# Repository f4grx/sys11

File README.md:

sys11
=====

This is a development board for the 68hc11 microcontroller.

The goal is to build a robust, simple, reliable, and repairable computer from
scrap, similar to what collapseOS is seeking.

The project defines two ROM images:
* a shell interface with assemble-time modular commands, development is halted.
* a forth interpreter.

Forth is a portable stack supported language wich is surprisingly powerful, even on
small targets. It has the potential to describe complex programs in a very compact way.

A lot of resources about forth are available online. This project defines a minimally small
forth interpreter with indirect threading. The goal is to build a 68hc11 interpreter that can
be used to write the interpreter itself, so it has to be as small as possible.

CPU: 68HC11A0, the most basic one. This is what I found in my drawer, and is
more desirable than a basic 6502 or other because it has integrated peripherals.
I only choose chips that I have replacement for.

Clock speed: 8 MHz XTAL / OSC, which translates to 2 MHz internal and
bus clock (Cycle time 500 ns). It seems that 16 MHz (4 MHz E clock, 250 ns
cycle) is also working. May switch to that later.

Currently sys11 is implemented on a protoboard using soldered 30AWG (wirewrap)
wires.

Memory map (HC11 extended mode)
-------------------------------

* Internal RAM kept mapped at 0x0000
* Memory Mapped Registers mapped at 0x0000 (unusual). They overlay the internal
RAM, which means internal RAM locations 00h..3Fh are not usable (except the
locations that are reserved or related to PORTB and PORTC: 0002h-0007h).

* 32KB On-board Main SRAM (62256) in 0000h - 7FFFh CSRAM = A15
* 16KB Off-board secondary SRAM (half 62256) in 8000h - BFFFh, possibly banked
for additional space using a IO register. Then we could use an even bigger RAM
chip. CSXRAM = !(A15 & !A14)
* 8KB I/O space with 8 CS lines in C000h - DFFFh (1KB per CS)
CSIO = !(A15 & A14 & !A13)
* 8KB EPROM in E000h - FFFFh - monitor and SPI flash loader. For development,
this chip can be replaced with a RAM/EEPROM/NVRAM, the board actually use a
DIL32 socket instead of 28, that exposes the nWR line. An additional pair of DIL
sockets can be used to route this signal to the actual /WR line of the debug
RAM. This is actually using a 27256 EPROM with 4 manually selected banks, to
allow for different boot images (asm, communications, shell, storage mgmt, TBD)
CSROM = !(A15 & A14 & A13)
* External bus lines are only driven when external bus is actually addressed.
It is not driven when the on-board memory (32K RAM, 8K ROM) is addressed.
CSEXT = CSIO & CSXRAM

Main address decoding can be done with a few NAND gates (7400 2-input, and 7410
3-input NAND gates).

Peripherals
-----------

* 5V power from USB
* SCI : (UART), TX and RX lines on a pin header for external communication.
10K pullups are installed to ensure proper behaviour in bootstrap mode where
PORTD is configured as open drain.
* HE10-40 connector for external bus. All lines buffered by 74xx245.

Seriously planned features
--------------------------

* Robust 5V power supply (LF50 LDO, max voltage 40V) with reverse voltage
protection
* Additional LM2575 step-down to reduce LDO heating (bypassable).
* 3 outputs (PORTA) dedicated as SPI CS selector lines (3 bits + 74138 decoder +
normal /SS line)
* I2C bus using discrete N-MOS transistor on OC lines to drive the bus in open
* Multi-VPP EPROM programmer on a secondary board
* Fully shielded aluminum enclosure for a 100x160 board

Planned vaporware features
--------------------------

* Removable SPI/I2C flash cardriges
* SCSI
* Ethernet
* MCP2515 SPI CAN
* Additional UARTs and various comm interfaces (fiber, RS422 RS485...)
* Wireless communication interfaces (AX.25, 1200 bauds packet modem)
* Audio cassette program storage (Kansas)
* Dual-port RAM in IO space for communication and shared mem with another HC11.

What is already done
--------------------
* Memory map
* Schematic (includes errors)
* I have some chips: 4x 68HC11A0, 1x 68HC11A1, 1x 68HC11E2 (thanks vince),
some 74xx245, 573, 138, 00, 10, 27256, various 32Kx8 and 8Kx8 RAMs
* Ordered a 2864 EEPROM from ebay (received, meanwhile I found another one in a junkbox)
* Bootstrap uploader in Python3.
* Working hardware prototype on 100x160 perforated board
* Clock, Reset, UART connection, power supply with decoupling
* Memory map decoder using logic gates
* The HC11 starts in bootstrap mode and successfully executes code to drive LED.
* The HC11 is able to select the expanded mode and test the 32K RAM without
  errors (and also a RAM in the dedicated 8K EPROM space).
* bootstrap program to load more memory. Initally planned to use a custom HDLC
  protocol, but will rather load S-records directly.
* IRQ lines from expansion board to cpu (were broken due to lack of pullups)

Summary: The system is validated on the soldered wirewrap euro board.

What remains to be done
-----------------------
* Editing schematic to fix errors and match reality of prototype
* Finish simulating all opcodes
* Replace fifth LS245 registers with sth that allows open drain on RST and IRQs.
* Determine next step for hardware. Secondary board with more RAM? EPROM programmer?
* NVRAM SSD using these old bq4017 samples maxim generously offered me for free
  multiple years ago (Unfortunately this board will be a one-of-a-kind add-on
  unless you have these chips available or are able to find enough RAM chips)
* Some kind of documentation storage using big EEPROMs (27C040/27C080) mapped in IO
  space using a 256-byte window. This would allow use as block storage. Same idea
  applies to the bq4017 nvrams.
* I2C bus hardware
* Design a smaller PCB that can fit in a smaller shielded box.

Software roadmap
----------------
* Bootloader for extended mode - DONE
* Malloc - WIP, almost validated
* Simulator - WIP
* Basic shell - ABANDONED
* SPI bus driver - Should workd
* Block device system - ABANDONED
* Forth - WIP

* SPI and/or I2C EEPROM driver
* I2C bus driver

Abandoned features that should be implementable in forth
--------------------------------------------------------
* Assembler
* Self host the system

Abandoned features that are useless or too complex
--------------------------------------------------
Or may be done later...
* ed-based text editor
* Definition of a position independent binary format
* IO kernel
* Program loader
* RTOS

SPI bus
-------
The HC11 hardware SPI bus wil be used in master mode.
* The SS line is used as OE for a 74138 decoder that provides 8 CS lines from
3 OC lines of port A.

I2C bus
-------
A proper i2c bus needs two bidirectionnal open drain lines, which are not
available on the HC11 if one wants to benefit from the hardware SPI block on
PORTD. Moreover, the HC11 does not have a hardware i2c, so bitbanging must be
used.

The i2c bus will be done on port A using Input Capture and Output Compare lines.
To read SDA and SCL, the IC1 and IC2 lines are used. To write the bus, the OC1
and OC2 lines are used to drive small BS170 MOSFETs. This requires inversion of
the bits to write, which is not a big problem for the driver.

FAQ
---
Q: Why move to Forth?

A: At first I did not want it, and I planned to build an assembler and shell to
be able to compile source assembly files and rebuild the system from itself.
While doable, this will use a lot of memory, both flash and RAM. Just a shell and
still-not-working block device system was using 800 bytes, or 1/10 of the rom space.

It is pitiful to have 8k of ROM and only be able to have an assembler program, and
nothing else.

Meanwhile CollapseOS, which was going in the same direction, realized the potential
of forth and started implementing it. I followed the movement for several reasons:
* Forth is portable, the same routines are able to work on "any" forth implementing
machine, whatever the underlying CPU. This greatly increases the potential of collapse
recovery machines.
* It is still possible to write an assembler in forth, even cross assemblers are possible,
which still increases the ability to mix different machine in a portable software environment.
* It has the potential to express quite complex software constructs in a very compact manner

Q: Why not use a 6502?

A: Because the 6502 has a 8-bit stack pointer which is ridiculously restrictive.
We are not anymore in the situation where the 6800 was $179 and the 6502 was $29.

A2: Going to forth, the underlying CPU is not so important since Forth can be implemented
on a variety of machines.

Q: Why not use a Z80?

A: Because I did not have one when I started this project. However, I plan to
have an assembler for this target. If you want to play with the Z80, have a
look at the RC2014 project and/or github.com/hsoft/collapseos.

The HC11 is a microcontroller, which usefully comes with an integrated UART and
SPI peripherals. The Z80 does not, so it requires external bus peripherals.
However, the Z80 can hook these devices to its IO bus, saving space for more RAM
on the memory bus.

At some point it may be more interesting to build a Z80 system, to benefit from
more RAM, and also more registers, even if the Z80 requires more cycles to
execute every instruction.

Other CPUs are also interesting to increase the potential for collapse recovery:
ARM and MSP430 are such interesting targets, even the x86.

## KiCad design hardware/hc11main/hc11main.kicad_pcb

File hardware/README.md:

sys11 hardware
===================

The most important part of this subproject is the schematic, that defines all
the components and their connection.

The circuit board can either be as a real two-sided PCB with SMD components for
compacity (the full SMD system can fit in a ebay 100x76x35 aluminium box).

But it can also be built on a pair of 100x160 prototyping boards, using a
HE10-40 and a ribbon cable, or a 64-pin Euro rack mount system. In that case,
connections can be either soldered or wirewrapped (!).

Design philosophy
-----------------
The secret goal of this project is to survive a technical apocalypse, even if
such an event is highly improbable and we would probably have more important
priorities than computers at that time.
Nevertheless, such a computer is interesting for educational purposes, and also
because it is likely much more robust and repairable than a modern computer.

BTW, if you want a more powerful computer, use an embedded ARM SoC (like stm32)
or a Raspberry Pi. However, if it breaks, dont ask me to fix it :p

Another goal of such a project is to allow programming of other computers
without having access to a more complex machine, so we will aim at developing
assemblers and uploaders for PIC, Arduino, and programmers for various memories
like EPROMS, EEPROMs, FLASHes, etc. that can be used in other designs.

Mini circuit board
------------------

The PCB and gerbers in this directory describe a board 100x70mm, that will fit
an ebay aluminium box of dimensions 100x76x35mm, using SMD components in SOIC
format. The resulting project is compact and somewhat repairable but requires a
lot of care not to burn the fine PCB traces. To help with repairs, each SMD
trace has two vias in it, which should reduce the risk of having lifted pads
when desoldering a SMD component. When desoldering a broken SMD component, it is
often desirable to limit PCB damage by cutting the chip leads with pliers, then
removing each of the still soldered leads one by one.

Connection between the two boards is achieved by a ribbon cable using straight pins
through the pcb, putting the ribbon cable in a u-shape. Board-to-board
stackable connectors can also be used.

Euro circuit board
------------------

This option is much larger but is much more robust than the mini circuit board.
All components can be removed and replaced, and connections can be reworked with
a lot of ease (just taking care not to burn the insulation of nearby wires).

Interconnections can use either soldered wirewrap 30AWG wire, or just plain
wirewrapping if sockets, tools and wires are available.

Connection between the two board is achieved by a ribbon wire on the side of the
boards, similar to what is used to connect IDE hard drives, except the full 40
pins are used, so the key usually found on IDE ribbon connector has to be
removed. The PCB is cut so that the socket and the plug of the ribbon do not
protrude outside of the euro board. This allows the user to build a simple and
robust metallic case from aluminum strips and flats.

Here is the current state of the prototype, top and bottom:

Enclosure
---------

Since one of the goal of this project is to bootstrap electronic circuits after
a civilization collapse, it is important to make sure that it can itself survive
the kind of difficult environment that may cause this collapse, including a
severe EMP event.

The only way to do that is to shield everything. So a proper metallic enclosure
has to be used. ebay has lot of extruded aluminium boxes suitable for both the
mini board and 100x160 boards. If the builder has machining resources, then it
is also possible to mill a box or build one from aluminium sheet and bars.

Connections are much more critical than the board itself. Since an EMP event
will induce high voltage in any wire that is not properly shielded, any
connector and opening in the project box is critical. I will only be using a
single SUB-D connector with the least amount of pins (probably 15). The
connector itself will receive a  metallic cover and will be disconnected when
the computer is not actively used.

Additional protections will be added on each electrical line crossing the box
through this SUBD connector: the possible components are gas discharge cells,
series resistors, and bidirectional transil diodes. The goal is to minimize the
impact of high voltages by reducing them to a low value if possible.

The ideal situation would be a single UART communication channel using
opto-isolated signals, like TOSLINK plastic optical fibers. Only the power supply would
then need severe EMP protections.

Prototype Progress
------------------

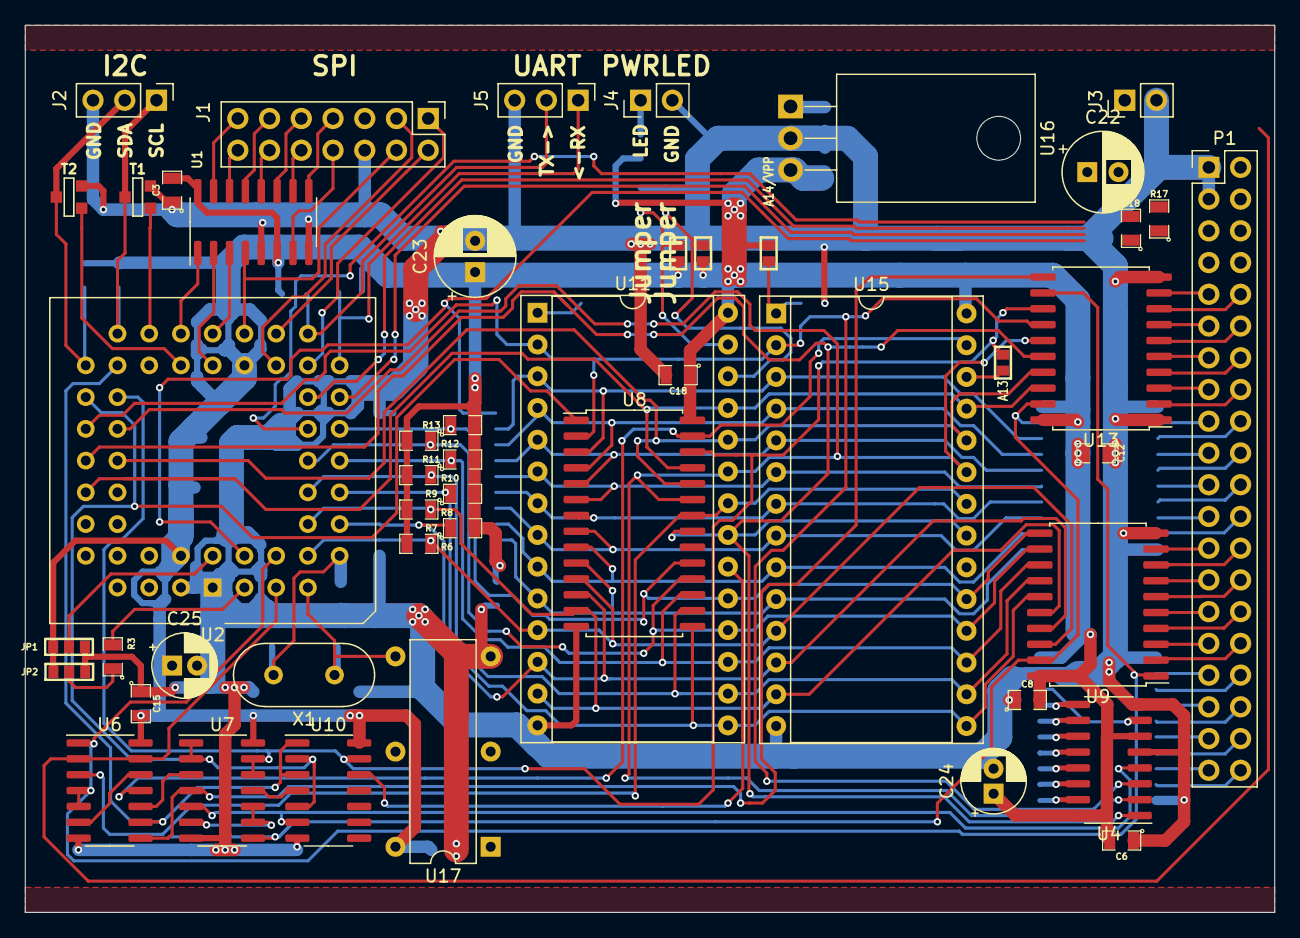
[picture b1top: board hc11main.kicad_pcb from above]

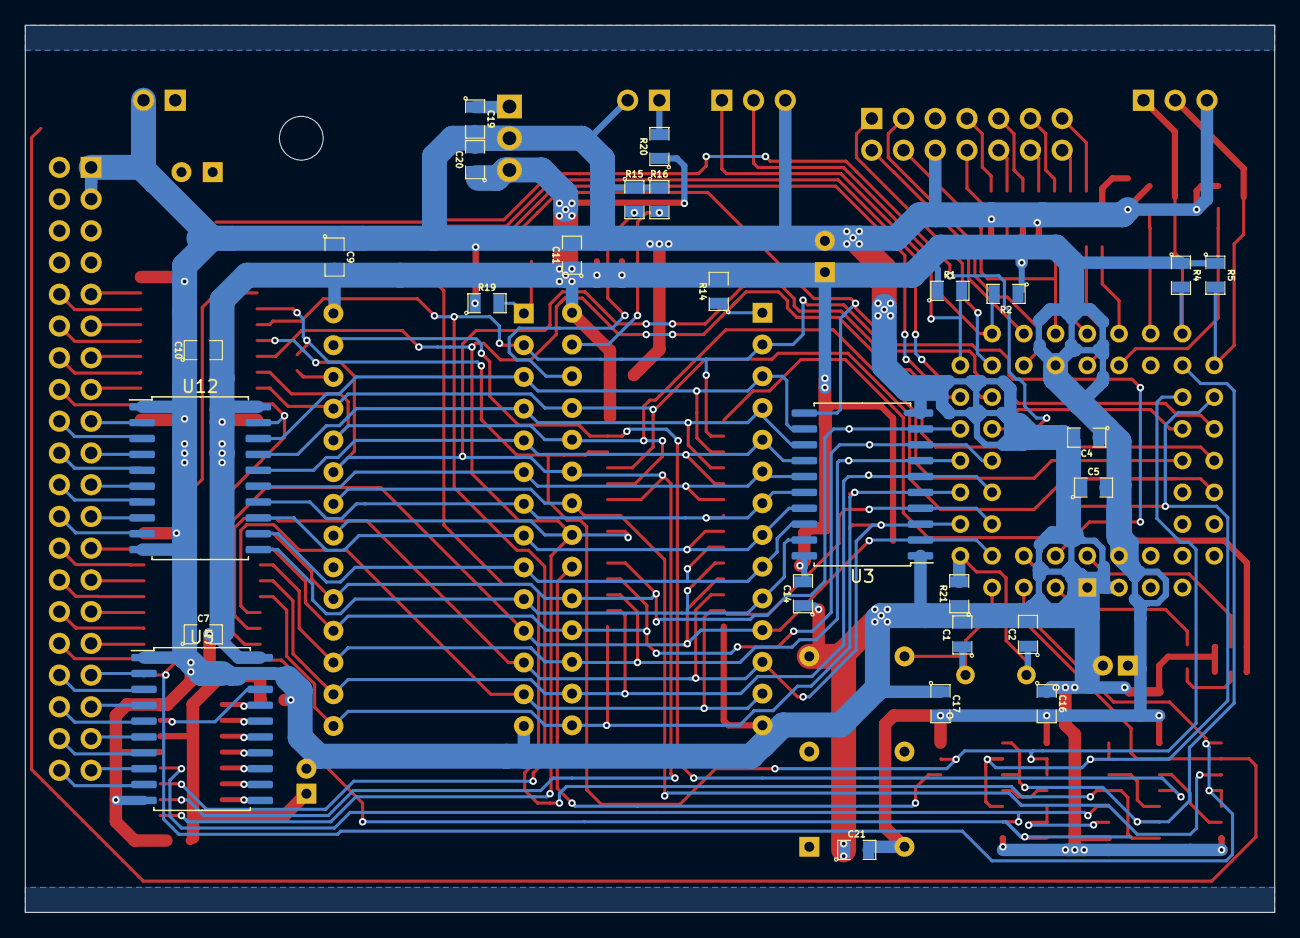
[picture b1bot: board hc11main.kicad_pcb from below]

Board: 2 copper layers, 100.0 x 71.0 mm, 76 parts (27 on the bottom side), 114 nets.

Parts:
C1, C2: CSMALL; 0805_m2012
C3, C6, C7, C8, C9, C10, C12, C14, C15, C16, C17, C19, C20, C21: 100n; 0805_m2012
C4: 10n; 0805_m2012
C5: 1u; 0805_m2012
C11, C18: 1uF; 0805_m2012
C22, C23: 100u; CP_Radial_D6.3mm_P2.50mm
C24, C25: 47u; CP_Radial_D5.0mm_P2.00mm
J1: SPI; PinHeader_2x07_P2.54mm_Vertical
J2: CONN_I2C; PinHeader_1x03_P2.54mm_Vertical
J3: CONN_PWR; PinHeader_1x02_P2.54mm_Vertical
J4: CONN_LED; PinHeader_1x02_P2.54mm_Vertical
J5: CONN_UART; PinHeader_1x03_P2.54mm_Vertical
JP1, JP2: Jumper3; SMDPADS_3
JP3: A13; SMDPADS_2
JP5, JP6: Jumper; SMDPADS_2
JP7: A14/VPP; SMDPADS_2
P1: CONN_2X20; PinHeader_2x20_P2.54mm_Vertical
R1, R2, R3, R6, R7, R8, R9, R10, R11, R12, R13, R21: 10k; 0805_m2012
R4, R5: 4k7; 0805_m2012
R14: 1k; 0805_m2012
R15, R16, R17, R18, R19: 100k; 0805_m2012
R20: RSMALL; 0805_m2012
T1, T2: BS170/2N7000 (SOT23); SOT23GDS
U1, U4: 74LS138; SOIC-16_3.9x9.9mm_P1.27mm
U2: 68HC11A0_PLCC; PLCC-52_THT-Socket
U3: 74LS573; SOIC-20W_7.5x12.8mm_P1.27mm
U5, U9, U12, U13: 74LS245; SOIC-20W_7.5x12.8mm_P1.27mm
U6, U7: 74LS00; SOIC-14_3.9x8.7mm_P1.27mm
U8: 62256; SOIC-28W_7.5x17.9mm_P1.27mm
U10: 74LS10; SOIC-14_3.9x8.7mm_P1.27mm
U11: 27256; DIP-28_W15.24mm_Socket
U15: 62256; DIP-28_W15.24mm_Socket
U16: 7805; TO-220-3_Horizontal_TabDown
U17: OSC_DIL14; DIP-OSCILLATOR
X1: 8 MHz; Crystal_HC49-U_Vertical

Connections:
/A0: U3.19, U8.10, U11.10, U12.11, U15.10
/A1: U3.18, U8.9, U11.9, U12.12, U15.9
/A2: U3.17, U8.8, U11.8, U12.13, U15.8
/A3: U3.16, U8.7, U11.7, U12.14, U15.7
/A4: U3.15, U8.6, U11.6, U12.15, U15.6
/A5: U3.14, U8.5, U11.5, U12.16, U15.5
/A6: U3.13, U8.4, U11.4, U12.17, U15.4
/A7: U3.12, U8.3, U11.3, U12.18, U15.3
/A8: U2.42, U8.25, U11.25, U13.18, U15.25
/A9: U2.41, U8.24, U11.24, U13.17, U15.24
/A10: U2.40, U4.1, U8.21, U11.21, U13.16, U15.21
/A11: U2.39, U4.2, U8.23, U11.23, U13.15, U15.23
/A12: U2.38, U4.3, U8.2, U11.2, U13.14, U15.2
/A13: JP3.2, U2.37, U7.12, U7.13, U8.26, U10.13, U13.13
/A14: U2.36, U7.1, U7.2, U8.1, U10.2, U10.5
/A15: U2.35, U6.9, U10.1, U10.3
/AS: U2.4, U3.11
/CSEN: J1.4, U1.4, U2.25
/D0: R6.1, U2.9, U3.2, U8.11, U9.18, U11.11, U15.11
/D1: R7.1, U2.10, U3.3, U8.12, U9.17, U11.12, U15.12
/D2: R8.1, U2.11, U3.4, U8.13, U9.16, U11.13, U15.13
/D3: R9.1, U2.12, U3.5, U8.15, U9.15, U11.15, U15.15
/D4: R10.1, U2.13, U3.6, U8.16, U9.14, U11.16, U15.16
/D5: R11.1, U2.14, U3.7, U8.17, U9.13, U11.17, U15.17
/D6: R12.1, U2.15, U3.8, U8.18, U9.12, U11.18, U15.18
/D7: R13.1, U2.16, U3.9, U8.19, U9.11, U11.19, U15.19
/E: U2.5, U6.2, U6.13
/EXTAL: C1.1, U2.7, U17.8, X1.1
/LED: J4.1, R20.2
/MISO: J1.1, U2.22
/MODA: R3.2, U2.3
/MODB: JP1.2, U2.2
/MOSI: J1.2, U2.23
/RXIN: J5.1, R1.2, U2.20
/R~W: U2.6, U6.1, U6.4, U6.5, U9.1, U13.12
/S0: U4.15, U5.11
/S1: U4.14, U5.12
/S2: U4.13, U5.13
/S3: U4.12, U5.14
/S4: U4.11, U5.15
/S5: U4.10, U5.16
/S6: U4.9, U5.17
/S7: U4.7, U5.18
/SCL: J2.1, R4.2, T1.D, U2.33
/SCLK: J1.3, U2.24
/SDA: J2.2, R5.2, T2.D, U2.34
/SPIA0: U1.1, U2.29
/SPIA1: U1.2, U2.28
/SPIA2: U1.3, U2.27
/SPICS0: J1.13, U1.15
/SPICS1: J1.14, U1.14
/SPICS2: J1.11, U1.13
/SPICS3: J1.12, U1.12
/SPICS4: J1.9, U1.11
/SPICS5: J1.10, U1.10
/SPICS6: J1.7, U1.9
/SPICS7: J1.8, U1.7
/TXOUT: J5.2, R2.2, U2.21
/VIN: C19.1, C22.1, U16.1
/XTAL: C2.1, R21.2, U2.8, X1.2
/bA0: P1.24, U12.9
/bA1: P1.23, U12.8
/bA2: P1.22, U12.7
/bA3: P1.21, U12.6
/bA4: P1.20, U12.5
/bA5: P1.19, U12.4
/bA6: P1.18, U12.3
/bA7: P1.17, U12.2
/bA8: P1.16, U13.2
/bA9: P1.15, U13.3
/bA10: P1.14, U13.4
/bA11: P1.13, U13.5
/bA12: P1.12, U13.6
/bA13: P1.11, U13.7
/bD0: P1.32, U9.2
/bD1: P1.31, U9.3
/bD2: P1.30, U9.4
/bD3: P1.29, U9.5
/bD4: P1.28, U9.6
/bD5: P1.27, U9.7
/bD6: P1.26, U9.8
/bD7: P1.25, U9.9
/bIRQ: P1.7, R18.1
/bR~W: P1.10, U13.8
/bS0: P1.40, U5.9
/bS1: P1.39, U5.8
/bS2: P1.38, U5.7
/bS3: P1.37, U5.6
/bS4: P1.36, U5.5
/bS5: P1.35, U5.4
/bS6: P1.34, U5.3
/bS7: P1.33, U5.2
/bXIRQ: P1.5, R17.1
/b~CSXRAM: P1.9, U13.9
/drSCL: T1.G, U2.31
/drSDA: T2.G, U2.30
/~A13: U7.11, U10.4
/~A14: U6.10, U7.3
/~CSEXT: U7.8, U9.19, U12.19, U13.19
/~CSIO: U4.4, U7.5, U10.6
/~CSROM: U10.12, U11.20
/~CSXRAM: U6.8, U7.4, U13.11
/~RD: U6.3, U8.22, U11.22, U15.22
/~WR: U6.11, U8.27, U15.27
GND: C1.2, C2.2, C3.1, C4.2, C5.1, C6.1, C7.1, C8.1, C9.1, C10.1, C11.2, C12.1, C14.1, C15.1, C16.1, C17.1, C18.2, C19.2, C20.2, C21.1, C22.2, C23.2, C24.2, C25.2, J1.6, J2.3, J3.2, J4.2, J5.3, JP1.3, JP2.3, P1.1, P1.3, R15.1, R16.1, R19.1, R21.1, T1.S, T2.S, U1.5, U1.8, U2.1, U2.51, U3.1, U3.10, U4.5, U4.8, U5.1, U5.10, U5.19, U6.7, U7.7, U8.14, U9.10, U10.7, U11.14, U12.1, U12.10, U13.1, U13.10, U15.14, U16.2, U17.7
unnamed: JP2.2, R3.1
unnamed: JP3.1, U15.26
unnamed: JP5.1, R16.2, U11.27
unnamed: JP6.1, R15.2, U11.26
unnamed: JP7.1, R19.2, U15.1
unnamed: R14.1, U11.1
unnamed: U6.6, U6.12
unnamed: U7.6, U7.9, U7.10
VCC: C3.2, C4.1, C5.2, C6.2, C7.2, C8.2, C9.2, C10.2, C11.1, C12.2, C14.2, C15.2, C16.2, C17.2, C18.1, C20.1, C21.2, C23.1, C24.1, C25.1, JP1.1, JP2.1, JP5.2, JP6.2, JP7.2, P1.4, P1.6, R1.1, R2.1, R4.1, R5.1, R6.2, R7.2, R8.2, R9.2, R10.2, R11.2, R12.2, R13.2, R14.2, R17.2, R18.2, R20.1, U1.6, U1.16, U2.26, U2.52, U3.20, U4.6, U4.16, U5.20, U6.14, U7.14, U8.28, U9.20, U10.14, U11.28, U12.20, U13.20, U15.28, U16.3, U17.14

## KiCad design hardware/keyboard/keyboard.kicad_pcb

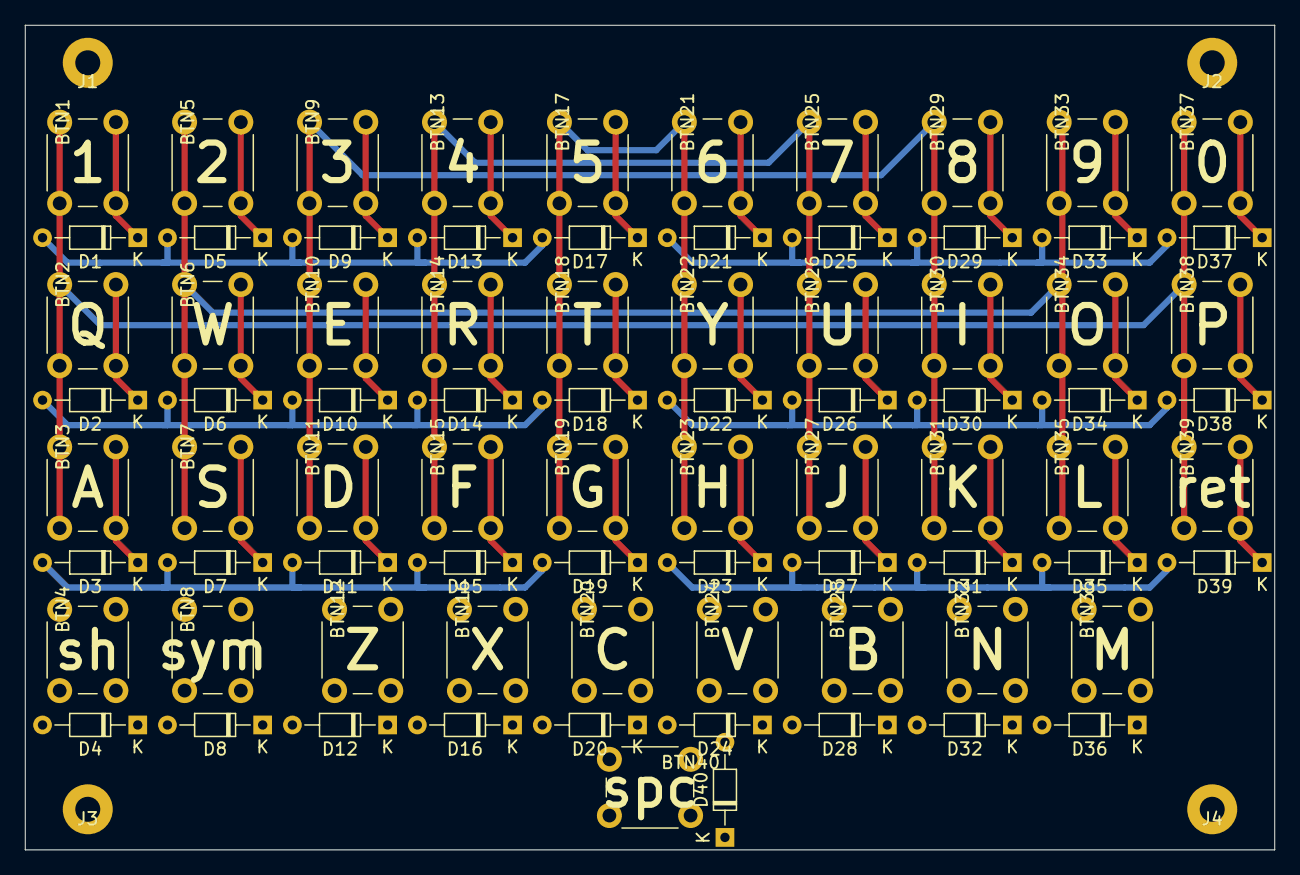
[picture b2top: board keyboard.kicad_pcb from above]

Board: 2 copper layers, 100.0 x 66.0 mm, 84 parts (0 on the bottom side), 53 nets.

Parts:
BTN1: 1; SW_PUSH_6mm
BTN2: Q; SW_PUSH_6mm
BTN3: A; SW_PUSH_6mm
BTN4: SHIFT; SW_PUSH_6mm
BTN5: 2; SW_PUSH_6mm
BTN6: W; SW_PUSH_6mm
BTN7: S; SW_PUSH_6mm
BTN8: SYM; SW_PUSH_6mm
BTN9: 3; SW_PUSH_6mm
BTN10: E; SW_PUSH_6mm
BTN11: D; SW_PUSH_6mm
BTN12: Z; SW_PUSH_6mm
BTN13: 4; SW_PUSH_6mm
BTN14: R; SW_PUSH_6mm
BTN15: F; SW_PUSH_6mm
BTN16: X; SW_PUSH_6mm
BTN17: 5; SW_PUSH_6mm
BTN18: T; SW_PUSH_6mm
BTN19: G; SW_PUSH_6mm
BTN20: C; SW_PUSH_6mm
BTN21: 6; SW_PUSH_6mm
BTN22: Y; SW_PUSH_6mm
BTN23: H; SW_PUSH_6mm
BTN24: V; SW_PUSH_6mm
BTN25: 7; SW_PUSH_6mm
BTN26: U; SW_PUSH_6mm
BTN27: J; SW_PUSH_6mm
BTN28: B; SW_PUSH_6mm
BTN29: 8; SW_PUSH_6mm
BTN30: I; SW_PUSH_6mm
BTN31: K; SW_PUSH_6mm
BTN32: N; SW_PUSH_6mm
BTN33: 9; SW_PUSH_6mm
BTN34: o; SW_PUSH_6mm
BTN35: L; SW_PUSH_6mm
BTN36: btn; SW_PUSH_6mm
BTN37: 0; SW_PUSH_6mm
BTN38: P; SW_PUSH_6mm
BTN39: RET; SW_PUSH_6mm
BTN40: SPC; SW_PUSH_6mm
D1, D2, D3, D4, D5, D6, D7, D8, D9, D10, D11, D12, D13, D14, D15, D16, D17, D18, D19, D20, D21, D22, D23, D24, D25, D26, D27, D28, D29, D30, D31, D32, D33, D34, D35, D36, D37, D38, D39, D40: DIODE; D_DO-34_SOD68_P7.62mm_Horizontal
J1, J2, J3, J4: PIN; HOLE_2mm_Keep4mm

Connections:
/1: BTN1.2, D1.K
/2: BTN5.2, D5.K
/COL1: D1.A, D5.A, D9.A, D13.A, D17.A
/COL2: D2.A, D6.A, D10.A, D14.A, D18.A
/COL3: D3.A, D7.A, D11.A, D15.A, D19.A
/COL4: D4.A, D8.A, D12.A, D16.A, D20.A
/COL5: D21.A, D25.A, D29.A, D33.A, D37.A
/COL6: D22.A, D26.A, D30.A, D34.A, D38.A
/COL7: D23.A, D27.A, D31.A, D35.A, D39.A
/COL8: D24.A, D28.A, D32.A, D36.A, D40.A
/Q: BTN2.2, D2.K
/ROW1: BTN1.1, BTN2.1, BTN3.1, BTN4.1, BTN37.1, BTN38.1, BTN39.1, BTN40.1
/ROW2: BTN5.1, BTN6.1, BTN7.1, BTN8.1, BTN33.1, BTN34.1, BTN35.1, BTN36.1
/ROW3: BTN9.1, BTN10.1, BTN11.1, BTN12.1, BTN29.1, BTN30.1, BTN31.1, BTN32.1
/ROW4: BTN13.1, BTN14.1, BTN15.1, BTN16.1, BTN25.1, BTN26.1, BTN27.1, BTN28.1
/ROW5: BTN17.1, BTN18.1, BTN19.1, BTN20.1, BTN21.1, BTN22.1, BTN23.1, BTN24.1
/W: BTN6.2, D6.K
unnamed: BTN3.2, D3.K
unnamed: BTN4.2, D4.K
unnamed: BTN7.2, D7.K
unnamed: BTN8.2, D8.K
unnamed: BTN9.2, D9.K
unnamed: BTN10.2, D10.K
unnamed: BTN11.2, D11.K
unnamed: BTN12.2, D12.K
unnamed: BTN13.2, D13.K
unnamed: BTN14.2, D14.K
unnamed: BTN15.2, D15.K
unnamed: BTN16.2, D16.K
unnamed: BTN17.2, D17.K
unnamed: BTN18.2, D18.K
unnamed: BTN19.2, D19.K
unnamed: BTN20.2, D20.K
unnamed: BTN21.2, D21.K
unnamed: BTN22.2, D22.K
unnamed: BTN23.2, D23.K
unnamed: BTN24.2, D24.K
unnamed: BTN25.2, D25.K
unnamed: BTN26.2, D26.K
unnamed: BTN27.2, D27.K
unnamed: BTN28.2, D28.K
unnamed: BTN29.2, D29.K
unnamed: BTN30.2, D30.K
unnamed: BTN31.2, D31.K
unnamed: BTN32.2, D32.K
unnamed: BTN33.2, D33.K
unnamed: BTN34.2, D34.K
unnamed: BTN35.2, D35.K
unnamed: BTN36.2, D36.K
unnamed: BTN37.2, D37.K
unnamed: BTN38.2, D38.K
unnamed: BTN39.2, D39.K
unnamed: BTN40.2, D40.K

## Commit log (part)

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2019-10-15 Write some specs
2019-10-15 add a bootloader readme
2019-10-17 ROM debug precisions
2019-10-18 start uart code
2019-10-21 Split uart definitions in an include file add a text file describing memory map
2019-10-28 prepare new options reset and run
2019-10-29 avoid using exceptions catch serial port open error rts reset no more a todo item
2019-10-30 use a generic makefile
2019-10-30 move linker script to a global location
2019-10-30 wait for transmit complete from bootstrap ROM loader last ACK
2019-10-31 some renames
2019-11-06 Add software roadmap
2019-11-06 More code to receive data frames
2019-11-06 stage2: improve buffer handling
2019-11-07 add a skeleton for a ROM monitori rework parts of uploader
2019-11-07 objdump for all sections
2019-11-08 Initial description of monitor
2019-11-08 add readme for board
2019-11-12 console: display correct chars
2019-11-12 ram test OK on my board!
2019-11-13 update docs
2019-11-13 fix more typos
2019-11-15 add separate makefile for bootstrap programs, add a memory dumper, reorg bootstrap ldscript to have multiple meaningful output sections
2019-11-15 even better build/link method
2019-11-15 monitor still does not run yet
2019-11-16 add /DATA poll to allow EEPROM programming (2864)
2019-11-17 cleanup bootloader dialog
2019-11-17 prepare memory manager
2019-11-18 normalize size of vectors zone, update tools readme with toolchain info
2019-11-19 add more doc
2019-11-20 uploader: search stage2.bin in another path
2019-11-20 add RRSF design document
2019-11-20 improve format (tables)
2019-11-20 add pics in hardware readme
2019-11-20 start writing the malloc routine use bss section for softregs properly allocate bss in the full linker
2019-11-20 rename main monitor file improve malloc attempt add sim info in monitor readme
2019-11-21 add doc for hc11 insns
2019-11-22 simplified malloc
2019-11-22 save 2 bytes by using D instead of Y, fix a bug with next->head
2019-11-27 simplify malloc for asm porting
2019-11-27 save one byte with clra/clrb instead of ldd #0
2019-11-27 finish instruction description
2019-11-27 save one byte in strlen, addd #1 is still very inefficient
2019-11-27 more memory map info in lkr
2019-11-29 malloc: translated asm to C for verification, still has emulation bugs
2019-12-01 add initial simulator code
2019-12-02 cut long lines, add core rw funcs, add getopt example from man page
2019-12-02 add addressing mode tables
2019-12-02 add net code in gdbremote, insns precisions
2019-12-03 able to execute write in INIT register
2019-12-03 implement BSET_DIR
2019-12-03 implemented RTS, uart init and puts are called and return!
2019-12-04 reorg opcodes in prep for flags computations
2019-12-04 some insn now set the flags
2019-12-04 improved fetch of B[R]SET/CLR, these now execute correctly
2019-12-09 more work on pull states
2019-12-09 add more opcodes, cycle limiting
2019-12-10 more work on signals
2019-12-10 gdb remote reports registers, ready for step/continue
2019-12-10 reorg commands, monitor works, prepare for target run ops
2019-12-11 messing with signals to avoid a global var when killing the gdb server
2019-12-14 fix malloc: block was not removed from list if it is not the first of free list!
2019-12-15 use softregs calling convention
2019-12-16 fixed addressing modes, add debug, map some ram that exists on the board, give names to mem zones
2019-12-16 single step, run, stop are working. Serious debugging can happen now.
2019-12-17 Fixed LDX (missed an adressing mode) Cleaned up notifs and connection/detach
2019-12-17 better support for prefixed ops, implement some branches.
2019-12-17 XGDX/Y, mm_alloc seems to run, going into mm_free
2019-12-17 some mode ld/st extended opcodes, async notif for Ctrl-C command, monitor now stops instead of wai.
2019-12-18 add function limit markers, introduce new file for shell
2019-12-18 prepare a getchar function
2019-12-18 cmdline acquisition code
2019-12-19 add some inc/cmp
2019-12-19 fix sci reception, now it works
2019-12-19 finish the serial terminal including raw input
2019-12-20 b[r][set/clr] for IND Y mode
2019-12-22 implement aba,sba,cba,deca.decb.nega,negb,neg,coma,comb,com,tsta,tstb,tst, also reorg some cases.
2019-12-23 add a doc to help design the assembler
2019-12-23 strcmp should work
2019-12-24 fix strlen and strcmp, shell commands are recognized. Also add function separators.
2019-12-24 implemented bitwise register operations. echo command is working.
2019-12-24 save 2 bytes on echo test, loose 3 on shell options init
2019-12-24 catch unimplemented opcodes in VECTOR_ILLEGAL for easier debugging. gdb remote reports SIGTRAP instead of SIGINT. Also started to rename opcode definitions to have the opcode value in the name.
2020-01-01 update project status
2020-01-07 add comments
2020-01-07 implement JMP
2020-01-07 Split command and arguments
2020-01-08 WIP argv
2020-01-08 fix cmd search with argv0
2020-01-08 implement lsld
2020-01-09 implement idiv, asld, adda, addb, adca, adcb
2020-01-09 implement BHI/BLS
2020-01-10 linker support for additional shell commands in other files
2020-01-10 add a dummy command for as11
2020-01-10 reduce CPU load by 100% by adding a sleep when the SCI is not receiving
2020-01-10 add device manager
2020-01-10 make sure full cmdlist is available, fix inttostr, start enum devices
2020-01-13 add design for a keyboard
2020-01-14 testing revealed a bug in arg parsing, to be fixed
2020-01-15 WIP - shell rework
2020-01-15 move buffers after state vars. this avois an unknown buffer overflow (TODO find it)
2020-01-15 ultra basic arg parse is ok
2020-01-15 Shell is now more modular. Functions could be reused. -shell_readline usable for ed text editor -shell_parse and shell_exec to interpret shell command files -shell_parse for assembler programs
2020-03-13 upload.py: select terminal baud rate monitor: disable blockdev stuff, configure uart at 9600 bauds monitor_apps: rename as11 to forth, assembler will be written in forth. TODO: replace whole shell wi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
2020-03-16 prepare for integration of forth interpreter instead of shell
2020-03-16 enable forth main app
2020-03-16 update readme, some preparatory code for forth execution
2020-03-17 add an absolute hc11 assembler
2020-03-17 make it build
2020-03-19 First bits of forth interpreter
2020-03-19 some more preparations
2020-03-20 add dolit
2020-03-20 some reorg, comments, branch opcodes
2020-03-23 add tool to dump dic
2020-03-24 Clarify the structure of words
2020-03-24 playing with file format to identify dic
2020-03-24 Inner interpreter works, anything called has to be an indirect reference and NEXT requires two indirections while saving the intermediate result of the indirection
2020-03-26 fix dup that requires incrementing by 2 not 1
2020-03-26 start implementing behaviours
2020-04-06 many more words
2020-04-14 implemented JNZD and TYPE, console acquisition and display should work
2020-04-16 fix linking, dic parser is now ok
2020-04-17 fix sim pulls, now CR is working, TODO IMMSTR/COUNT/TYPE
2020-04-17 fix native stack ops, TYPE is close to working but not yet
2020-04-17 console works: ACCEPT and TYPE are ok. However extremely small on the simulator. to be tested on real hardware at 8 MHz
2020-04-23 execute is a jump that will interrupt the current word and branch to a new one. so calling it directly from EVAL was stopping the interpretation of further words. EXECUTE has to be launched from a su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
2020-04-24 makefile cleanup
2020-04-24 only delay main loop when core is stopped
2020-04-24 turn all word names into counted strings remove some names that will only be used for compilation
2020-04-25 typo
2020-04-27 Add code for R@ and SAME?, prepare FIND
2020-04-27 implement dupz and cells
2020-04-28 improve str compare, no more stack error. csame stubbed, TODO
2020-04-29 save a word
2020-04-29 fix parser to display words without header remove more debug words and cleanup prompt
2020-04-29 add sim speed indication
2020-04-30 implemented inherent rotates
2020-05-01 progress but not ok yet Testing on real hc11 cpu is OK, so we have a simulator bug. maybe in the recently implemented ROT?
2020-05-02 add words for number output (seems broken) add instruction counter stats add initial code to allow core testing to find core bugs
2020-05-04 fix confusion between HOLD word and HOLDP address
2020-05-04 Support simulation interruption on core execution of STOP
2020-05-04 add a doc file
2020-05-04 remove a debug in gdbremote
2020-05-04 cleanup program output, add unit test for ROLA,ROLB
2020-05-04 fix a fundamental flaw in EXECUTE that previously could only run forth words (not native ones) in a bad way by just jumping at the next word instead of running the code pointer of the word! Now numer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
2020-05-06 add SP@, use to debug. still not working.
2020-05-06 add code to display regs in debug mode and correct display of int64 values
2020-05-06 INTERPRETER WORKS! remove lots of debug fix S@ name length
2020-05-07 implement basic text output and comments
2020-05-07 implemented catch
2020-05-07 implement THROW and manage parse errors
2020-05-08 rework IMMSTR to allow other words to be followed by string litterals, like abortz. implement STACK? to check underflow, it does not work because inner interpreter also need a stack bucket to jump to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
2020-05-09 forth: document two versions for opcode execution. forthdic.py: add support for abortz string immediates
2020-05-11 add the first words for compilation
2020-05-11 split ccompare and namecompare to allow for immediate and compile_only flags
2020-05-11 headers for structure words python dic parser handles flags in name lengths
2020-05-12 implement KEY with KEY?, implement NUF? (seems broken), MIN, MAX, U.R, .R, SPACES, TCHAR, and some tools : _TYPE, dm+, DUMP, .S
2020-05-13 detect immediate words to execute them in compilation mode (doesnt work yet)
2020-05-13 update python tool to generate word list and graphviz file, update these files
2020-05-13 avoid edges to return
2020-05-13 avoid edges to branch
2020-05-13 This compiler manages to assemble a word, but creates a bad header. TOFIX but good start.
2020-05-14 compiler works and compiled words can be executed
    : TEST 123 . ; ok
    $100 20 DUMP
    100 F1 55 4 54 45 53 54 E0 33 E1 53 0 7B E7 CC E1 qU_TEST`3aS_{gLa
    110 51 4 44 55 4D 50 0 0 0 0 0 0 0 0 0 0 Q_DUMP__________ ok
    TEST 123 ok
    \o/
2020-05-14 introduce SHOWSTR to replace IMMSTR...COUNT TYPE ABORTZ -> ABORTNZ Interpreter now detects compile-only words Fixed inline string compilation (scompq) Implement compile-time ABORT" ." and $" factoriz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
2020-05-15 vectorize IO words to allow IO redirection
2020-05-15 Implenting DOES with some success. Testing with: : INH CREATE C, DOES> C@ C, ; ok 42 INH NOP ok $100 64 DUMP 100 F2 9C 3 49 4E 48 E0 2B EF FD ED D1 E1 57 1 1A r__INH`+o}mQaW__ 110 E1 57 0 54 E1 9B E1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
2020-05-18 prepare UM* hardware routine
2020-05-19 start working towards F2012 compliance
2020-05-19 document source to indicate F2012 status and start doing easy changes
2020-05-19 build fixes
2020-05-19 save some ROM with INC,DEC,CHARP instead of IMM,1,PLUS/SUB
2020-05-19 rename FIND/ISNAME to FINDONE/FIND, towards F2012 compliance
2020-05-20 compile only words cannot be found anymore in interpretation state
2020-05-22 implemented IMMEDIATE
2020-05-22 Implement CLEAR to setup HERE, remove associated asm code, prepare FORGET.
2020-05-22 interpretation works again with FIND based on TRAVERSE-WORDLIST
2020-05-25 initialize LASTP in forth, now initial asm code is the bare minimum rename COMPILE to COMPILE_IMM (only an internal word) and rename [COMPILE] to POSTPONE (usable in colon defs).
2020-05-25 start writing div3216 code
2020-05-25 hardware div3216 alg is OK, thanks FGR
2020-05-26 Validated hardware UM/MOD on several pathological cases. Used 5 more asm bytes. Examples that were previously failing: 57479 24148 56224 UM/MOD U. U. 28148 27655 ok 17320 1738 2868 UM/MOD U. U. 39720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
2020-06-10 main board: continue routing
2020-06-26 almost completed routing
2020-06-29 move main board to its own repo
